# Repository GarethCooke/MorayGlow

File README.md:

# MorayGlow

IoT LED strip controller — ESP32 firmware + web UI with Home Assistant integration.

## Project Summary

MorayGlow controls an RGB LED strip via an **ESP32**. The device hosts a web UI and exposes a REST + WebSocket API. A browser-based client lets you toggle the strip on/off and pick a colour. The device also integrates with **Home Assistant** via MQTT auto-discovery, so it appears automatically as a light entity.

## Project Structure

```text
MorayGlow/
├── MorayServer/               # ESP32 firmware (C++, PlatformIO)
│   ├── platformio.ini
│   ├── src/main.cpp            # WiFi, LittleFS, REST API, WebSocket
│   ├── include/
│   │   ├── config.h            # WiFi credentials, MQTT config — edit before flashing
│   │   ├── state.h             # Pure logic: stateToJson, rgbToHex, parseMqttCommand
│   │   └── mqtt.h              # MQTT client + Home Assistant discovery
│   └── test/
│       └── test_state.cpp      # Unity tests (run on host, not device)
└── MorayClient/               # Web UI (plain HTML/CSS/JS — no framework)
    ├── index.html
    ├── css/style.css
    ├── js/
    │   ├── moray.js           # UMD utility module (buildWsUrl, isValidHexColor)
    │   └── app.js              # Main UI logic
    ├── test/
    │   └── moray.test.js      # Jest tests for moray.js
    └── test-server/            # Node.js mock server for UI development
        ├── server.js
        ├── logic.js            # Pure functions (testable without starting server)
        ├── db.json             # Persisted state between restarts
        └── test/
            └── server.test.js  # Jest tests for logic.js
```

## API

| Method | Endpoint       | Body                    | Description                                   |
| ------ | -------------- | ----------------------- | --------------------------------------------- |
| GET    | `/api/state`   | —                       | Returns `{"on": bool, "color": "#rrggbb"}`    |
| POST   | `/api/power`   | `{"on": bool}`          | Turn strip on or off                          |
| POST   | `/api/color`   | `{"color": "#rrggbb"}`  | Set strip colour                              |
| WS     | `/ws`          | —                       | Server pushes state on every change           |

## Design Decisions

| Decision       | Choice                                          | Reason                                                  |
| -------------- | ----------------------------------------------- | ------------------------------------------------------- |
| MCU            | ESP32 Dev Board                                 | Dual-core, Wi-Fi + Bluetooth built in                   |
| Build system   | PlatformIO                                      | Dependency management, board config, native test env    |
| Web server     | `esphome/ESPAsyncWebServer-esphome`             | Supports ESP32; async                                   |
| Filesystem     | LittleFS                                        | Serves client files from device flash                   |
| JSON           | ArduinoJson v7 (`JsonDocument`)                 | No capacity arg needed; widely supported                |
| MQTT           | `knolleary/PubSubClient` + `setBufferSize(512)` | Lightweight, well-maintained                            |
| HA integration | MQTT auto-discovery                             | Device appears automatically in Home Assistant          |
| Client         | Plain HTML/CSS/JS (no framework)                | Keeps LittleFS footprint small                          |
| Client module  | UMD pattern (`moray.js`)                       | Works as browser global and Node.js/Jest module         |
| Testability    | Pure functions in `state.h` / `logic.js`        | Compiled and tested on host without hardware            |
| C++ tests      | Unity (via PlatformIO native env)               | Bundled with PlatformIO; runs on host                   |
| JS tests       | Jest                                            | Standard, zero-config for CommonJS modules              |

## Before Flashing

Edit `MorayServer/include/config.h` and set your WiFi SSID/password and MQTT broker IP before building and flashing.

## Running Tests

### MorayServer — C++ firmware (Unity via PlatformIO)

Requires `gcc`/`g++` on your PATH (install MinGW-w64 if not present).

```powershell
cd MorayServer
pio test -e native
```

### MorayClient — browser JS logic (Jest)

```powershell
cd MorayClient
npm install   # first time only
npm test
```

### Test server — Node.js logic (Jest)

```powershell
cd MorayClient\test-server
npm install   # first time only
npm test
```

---

## Starting the Test Server

The test server lets you develop and test the web UI without the physical device.

```powershell
cd MorayClient\test-server
npm install   # first time only
npm start
```

Then open [http://localhost:3000](http://localhost:3000) in a browser.

State is persisted to `MorayClient\test-server\db.json` between restarts.

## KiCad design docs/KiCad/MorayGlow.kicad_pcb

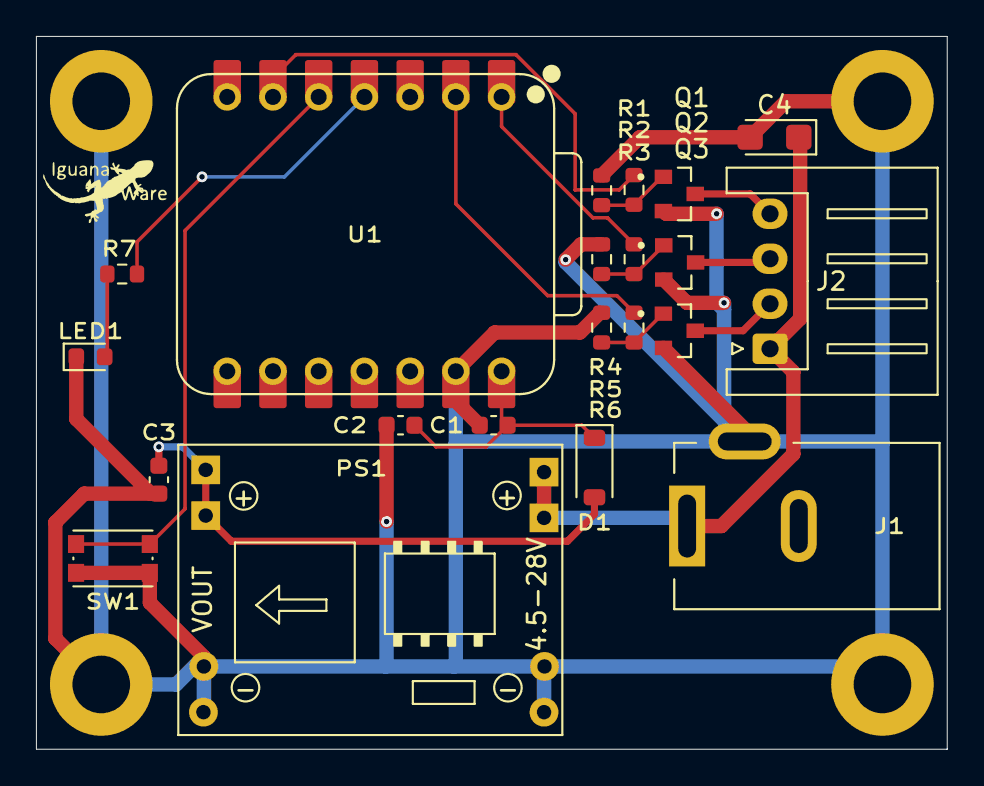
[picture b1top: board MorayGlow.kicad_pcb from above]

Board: 2 copper layers, 50.6 x 39.6 mm, 25 parts (0 on the bottom side), 16 nets.

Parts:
C1, C3: 0.1uF; C_0603_1608Metric
C2: 10uF; C_0603_1608Metric
C4: 100uF; CP_EIA-3216-18_Kemet-A
D1: 1N5819HW-7-F; D_SOD-123
H1, H2, H3, H4: Hole_Pad; MountingHole_3.2mm_M3_ISO7380_Pad
J1: Barrel Jack; BarrelJack_Kycon_KLDX-0202-xC_Horizontal
J2: RGB LED; JST_XH_S4B-XH-A_1x04_P2.50mm_Horizontal
LED1: LED; LED_0603_1608Metric
PS1: MP1584 5V buck module; SRT_MPT1584EN_Module
Q1, Q2, Q3: IRLML6344TRPBF; TRANS_IRLML6344TRPBF
R1, R2, R3: 100; R_0603_1608Metric
R4, R5, R6: 100k; R_0603_1608Metric
R7: 330; R_0603_1608Metric
SW1: SW_DIP_x01; SW_Push_1P1T_NO_CK_KMR2
U1: XIAO-ESP32-S3-Plus-SMD; XIAO-ESP32-S3-DIP

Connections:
CMD_BTN: SW1.1, U1.5 (GPIO5_A4_D4_SDA)
GND: C1.2, C2.2, C3.1, C4.2, H1.1 (1_1), H2.1 (1_1), H3.1 (1_1), H4.1 (1_1), J1.3, LED1.1 (K), PS1.2, PS1.4, Q1.2, Q2.2, Q3.2, R4.2, R5.2, R6.2, SW1.2, U1.13 (GND)
LED_B: J2.4, Q1.3
LED_G: J2.2, Q3.3
LED_R: J2.3, Q2.3
unnamed: C1.1, C2.1, D1.1 (K), U1.14 (VBUS)
unnamed: LED1.2 (A), R7.1
unnamed: Q1.1, R1.1, R4.1
unnamed: Q2.1, R2.1, R5.1
unnamed: Q3.1, R3.1, R6.1
RGB_B: R1.2, U1.6 (GPIO6_A5_D5_SCL)
RGB_G: R3.2, U1.2 (GPIO2_A1_D1)
RGB_R: R2.2, U1.1 (GPIO1_A0_D0)
STATUS_LED: R7.2, U1.4 (GPIO4_A3_D3)
VCC_12V: C4.1, J1.1, J2.1, PS1.1
VDD_5V: C3.2, D1.2 (A), PS1.3

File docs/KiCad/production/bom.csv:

Designator,Footprint,Quantity,Value,LCSC Part #
"C1, C3",0603,2,0.1uF,
C2,0603,1,10uF,
D1,D_SOD-123,1,1N5819HW-7-F,
J2,JST_SH_SM04B-SRSS-TB_1x04-1MP_P1.00mm_Horizontal,1,RGB LED,
J5,BarrelJack_Kycon_KLDX-0202-xC_Horizontal,1,Barrel Jack,
LED1,0603,1,LED,
PS1,SRT_MPT1584EN_Module,1,MP1584 5V buck module,
"Q1, Q2, Q3",SOT-23,3,IRLML6344TRPBF,
"R1, R2, R3",0603,3,100,
"R4, R5, R6",0603,3,10k,
R7,0603,1,330,
SW1,SW_Push_1P1T_NO_CK_KMR2,1,SW_DIP_x01,
U1,XIAO-ESP32-S3-DIP,1,XIAO-ESP32-S3-Plus-SMD,

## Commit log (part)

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2026-04-10 Initial commit — graduated from Arduino mono-repo
2026-04-16 final changes before fabrication
2026-04-28 updated pcb imags - new pcb
